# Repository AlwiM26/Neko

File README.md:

# Neko

A custom version of the [Chocofi keyboard](https://github.com/pashutk/chocofi). With slightly different edge cut and added custom silkscreen.

## List of changes

- Slight change from the original edge cut
- Remove the inner ( 3rd ) thumb key
- Add some graphic for the silkscreen

## Assembly

- Solder all the diode on the bottom side, make sure to solder it to the correct orientation like this
  
- Solder all the kailh hotswap socket on the bottom side
- ( Optional for **wireless** build )Solder power switch on the bottom side, after that, make sure to switch it off so that nothing happen when we solder the battery
  
- Solder the reset switch on the top side
- ( Optional for **wired** build) Solder the TRRS connector on the top side
- Solder the controller hotswap socket on the top side
- Solder the hotswap pin to the controller
- Remove the controller from the hotswap socket
- ( Optional for **wireless** build ) _Carefully_ solder battery wires to the connector, ensuring not to short the wires together, secure the other wire with masking tape, solder the black wire to the negative pad, and red wire to the positive pad
  
- ( Optional for **wireless** build ) Solder the battery Jumper ( labeled as RAW ) on the bottom side

If you using a wireless controller, you can download my firmware [here](https://github.com/AlwiM26/zmk-config-neko/actions), or you can build your own firmware using the [ZMK firmware](https://zmk.dev), and edit the keymap using the [Keymap editor](https://nickcoutsos.github.io/keymap-editor/) by Nickcoutsos. If you using a wired controller, you can use [QMK firmware](https://qmk.fm/), and edit the layout using [Via app](https://www.caniusevia.com/)

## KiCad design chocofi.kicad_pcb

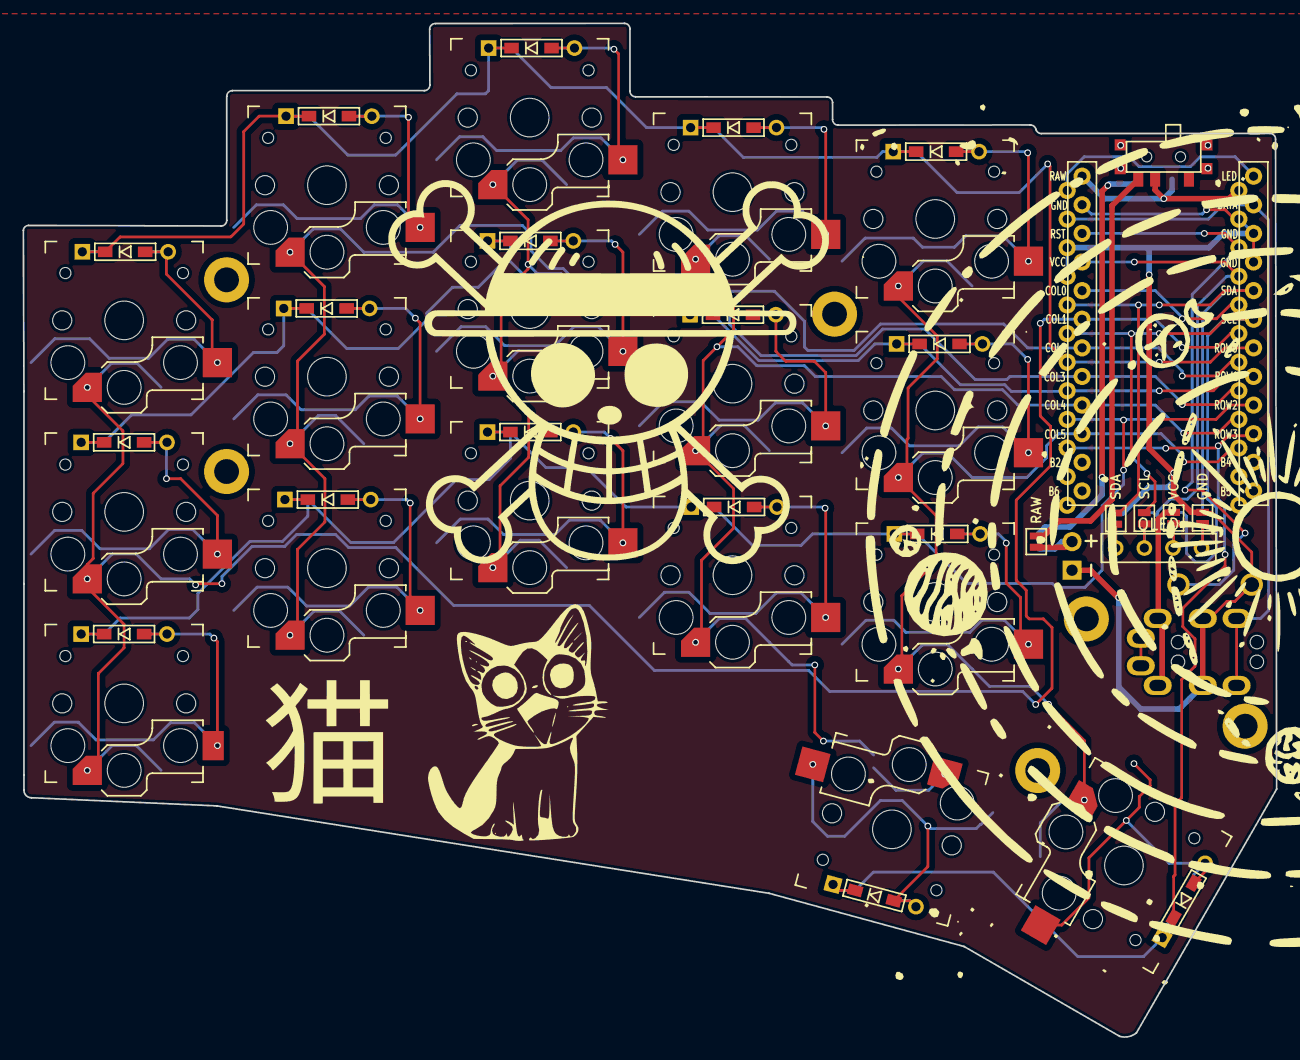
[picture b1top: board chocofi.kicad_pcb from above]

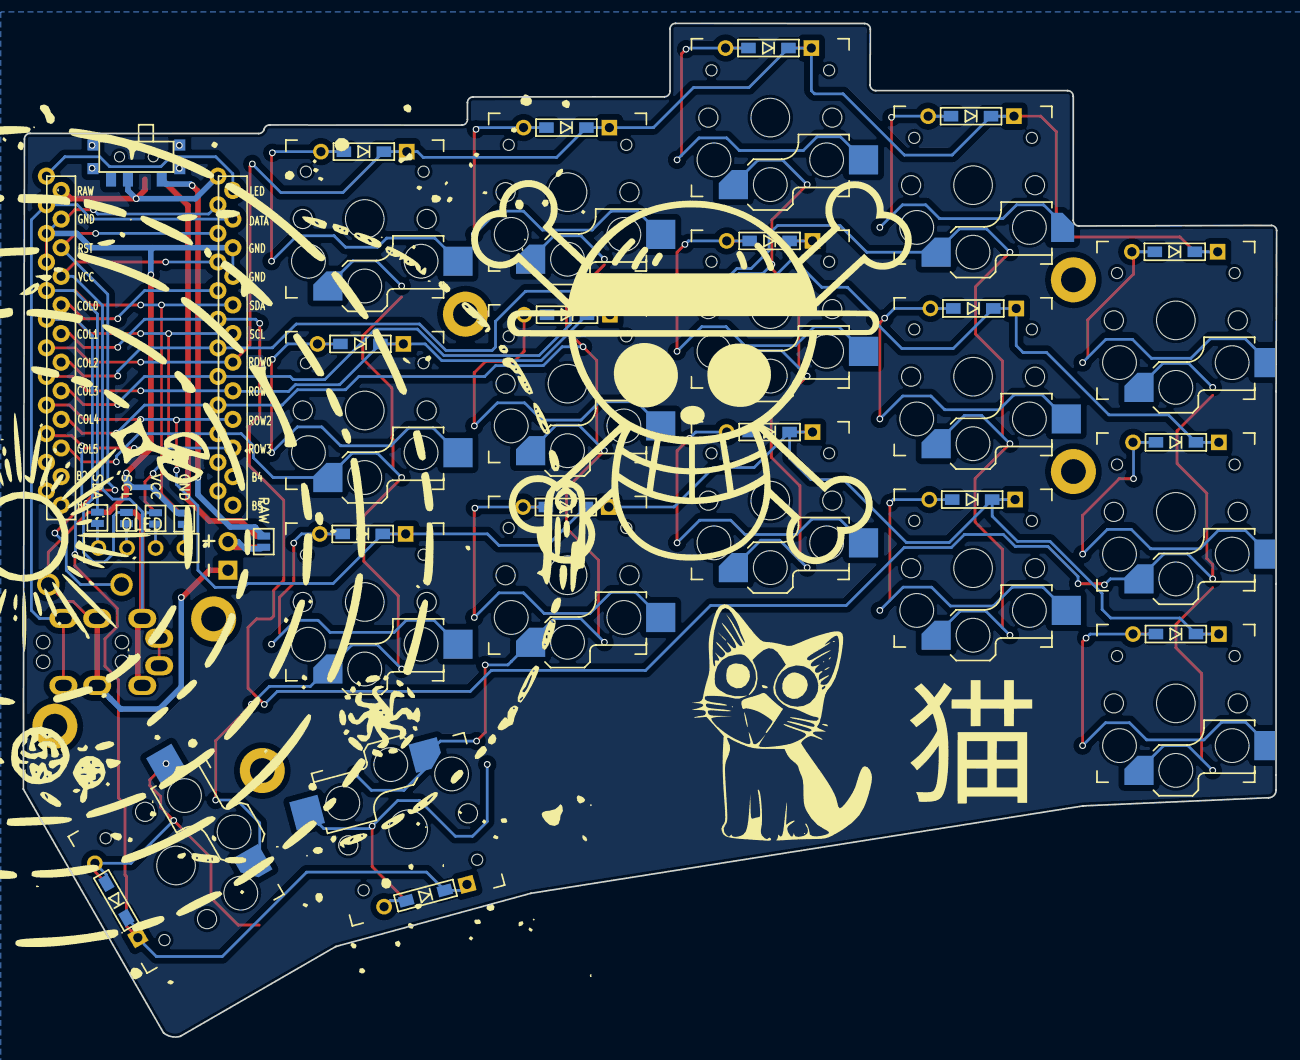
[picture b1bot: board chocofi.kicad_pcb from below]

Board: 2 copper layers, 111.3 x 90.0 mm, 57 parts (6 on the bottom side), 39 nets.

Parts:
D2, D3, D4, D5, D6, D8, D9, D10, D11, D12, D14, D15, D16, D17, D18, D20, D21: D; D3_TH_SMD
H1: h1; LEGO_HOLE
J1: MJ-4PP-9
J2: OLED
J3: Conn_01x02_Female; Battery_TH
JP6, JP61: SDA; Jumper
JP61#2, JP62#2: RAW; Jumper
JP62, JP68: GND; Jumper
JP63, JP66: SCL; Jumper
JP64, JP65: VCC; Jumper
RSW1: Val**; ResetSW
SW1, SW2#2: SW_SPDT; SW_SPDT+H-MSK12C01_hor(7pin_SMD)
SW2, SW3, SW4, SW5, SW6, SW8, SW9, SW10, SW11, SW12, SW14, SW15, SW16, SW17, SW18, SW20, SW21: SW_PUSH; Kailh_socket_PG1350_reversible
U1: ProMicro; ProMicro_v2
h2: h2; LEGO_HOLE
h3: h3; LEGO_HOLE
h5: h5; LEGO_HOLE
h6: h6; LEGO_HOLE
h7: h7; LEGO_HOLE

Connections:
BAT_PLUS: J3.2, JP61#2.2, JP62#2.2
GND: J1.C, J3.1, JP62.1, JP68.1, RSW1.1, U1.3, U1.4, U1.23
unnamed: D2.2, SW2.2
unnamed: D3.2, SW3.2
unnamed: D4.2, SW4.2
unnamed: D5.2, SW5.2
unnamed: D6.2, SW6.2
unnamed: D8.2, SW8.2
unnamed: D9.2, SW9.2
unnamed: D10.2, SW10.2
unnamed: D11.2, SW11.2
unnamed: D12.2, SW12.2
unnamed: D14.2, SW14.2
unnamed: D15.2, SW15.2
unnamed: D16.2, SW16.2
unnamed: D17.2, SW17.2
unnamed: D18.2, SW18.2
unnamed: D20.2, SW20.2
unnamed: D21.2, SW21.2
unnamed: J2.3, JP65.2, JP66.2
unnamed: J2.4, JP6.2, JP68.2
unnamed: J2.2, JP63.2, JP64.2
unnamed: J2.1, JP61.2, JP62.2
unnamed: SW1.2 (B), SW2#2.2 (B), U1.24
SCL: JP63.1, JP66.1, U1.6
SDA: JP6.1, JP61.1, U1.5
SW_RAW_2: JP61#2.1, SW1.3 (C)
VCC: J1.D, JP64.1, JP65.1, U1.21
col1: SW2.1, SW8.1, SW14.1, U1.19
col2: SW3.1, SW9.1, SW15.1, U1.18
col3: SW4.1, SW10.1, SW16.1, U1.17
col4: SW5.1, SW11.1, SW17.1, SW20.1, U1.16
col5: SW6.1, SW12.1, SW18.1, SW21.1, U1.15
data: J1.B, U1.2
reset: RSW1.2, U1.22
row0: D2.1, D3.1, D4.1, D5.1, D6.1, U1.7
row1: D8.1, D9.1, D10.1, D11.1, D12.1, U1.8
row2: D14.1, D15.1, D16.1, D17.1, D18.1, U1.9
row3: D20.1, D21.1, U1.10

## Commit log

2024-10-13 initialize commit and add LICENSE
2024-10-13 add gerber file
2024-10-13 Adding kicad project file
2024-10-13 Added README and images
2024-10-13 fix the image link
2024-10-22 Add backplate and case
2024-10-23 add case file
2024-10-23 Added case with battery support
2024-10-25 Add controller cover
2024-10-26 fix readme, cleaning up
2024-11-05 Fix the case fitting
2025-05-17 Add neko firmware link
